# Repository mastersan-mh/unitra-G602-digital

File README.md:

I apologize to non-Russian-speaking users for the lack of information in English.

Данный проект был начат мной как попытка реанимировать старый электрофон Вега 119 с ЭПУ Unitra G602
(А ещё я люблю музыку и программирование).
Поскольку у оригинального устройства аналоговая плата управления пришла в полную негодность,
мной было принято решение о разработке цифрового управления.

В качестве платформы я выбрал Arduino Nano на микроконтроллере ATmega328p.
Это сильно упростило разработку платы и монтаж микросхем, особенно учитывая то, что это штучное устройство,
и весь монтаж я планировал провоизводить на макетную плату, используя только выводные компоненты.

Я процессе модернизации я старался как можно меньше модифицировать оригинальный компоненты,
однако, модификации подверглись:

1. Ведомый шкив. К нему снизу были приклеены 8 флажков.
Поскольку мне неизвестно передаточное число для шкива мотора и шкива диска,
я снимаю показания о скорости непосредственно со шкива диска.
Флажки изначально были подобраны такой высоты, чтобы шкив задевал ими за стол и не вращался.
Для того чтобы флажки стали нужной высоты, я покрыл наждачной бумагой стол ЭПУ, и несколько раз повернул шкив вокруг оси.
Как результат, флажки сточились до необходимой высоты.

2. В столе было прорезано одно отверстие, для того чтобы поместить туда оптический датчик для снятия показаний вращения диска,
и расширено одно из отверстий, чтобы в него вставить оптический датчик вращения двигателя.
Оригинальный датчик я не стал оставлять, поскольку его характеристики мне неизвестны,
а так же был сломан держатель лампы, которая освещала его.

3. Крепление двигателя было модифицировано, чтобы в него можно было вставить датчик вращения.

4. Оригиналная лампа стробоскопа была заменена на светодиод, который к тому же используется для индикации состояний.

5. Немного пришлось отрегулировать флажок автостопа, поскольку новый датчик немного не попал на то место, где находился старый датчик.

На самом деле, датчик вращения двигателя не нужен, я решил его установить в качестве эксперимена.

2019-09-29

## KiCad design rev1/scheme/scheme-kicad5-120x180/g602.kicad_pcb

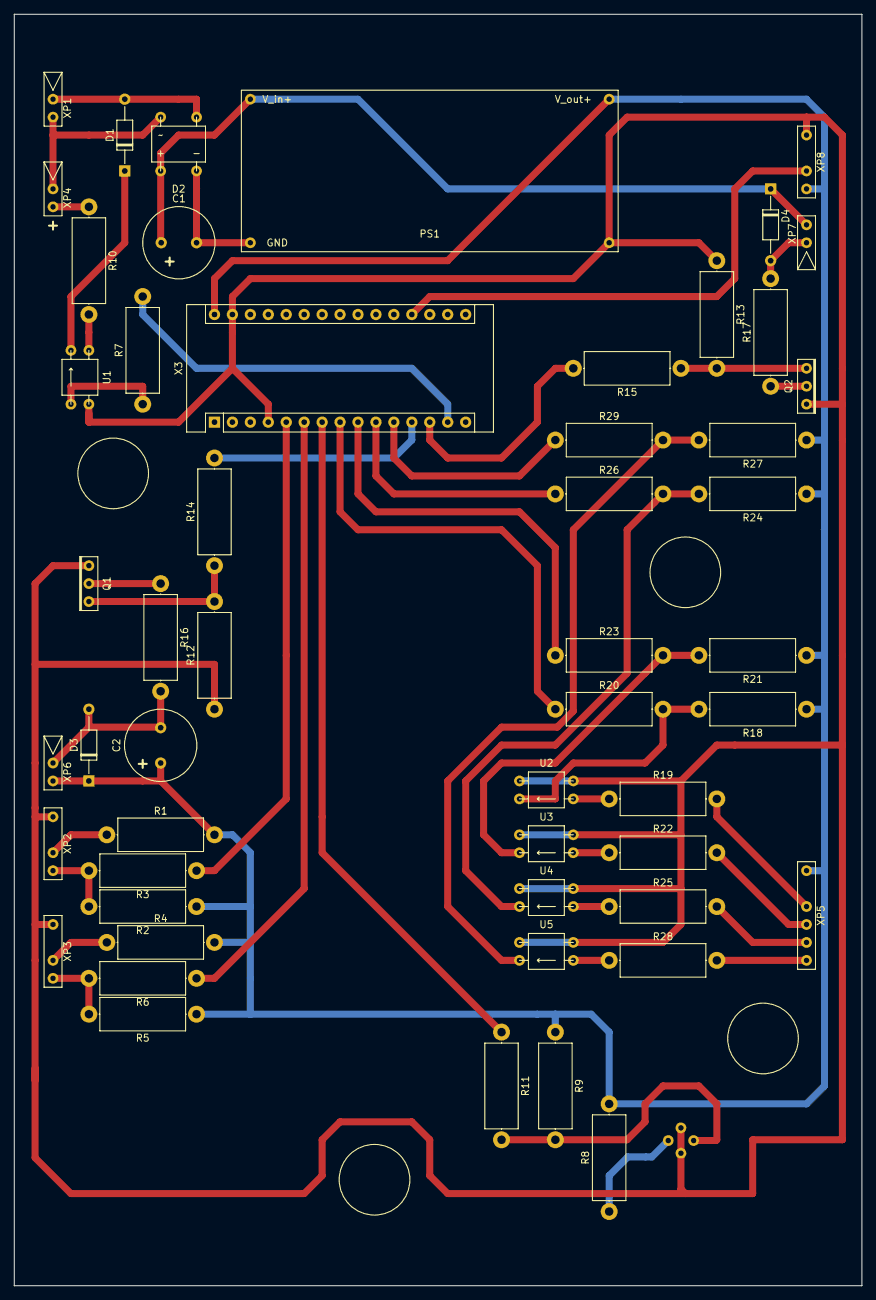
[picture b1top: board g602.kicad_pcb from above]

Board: 2 copper layers, 120.0 x 180.0 mm, 53 parts (1 on the bottom side), 45 nets.

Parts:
C1: 2500uF; C_Radial_D10.0mm_H12.5mm_P5.00mm
C2: 2200uF; C_Radial_D10.0mm_H12.5mm_P5.00mm
D1, D3, D4: D; D_DO-35_SOD27_P10.16mm_Horizontal
D2: DF01M
PS1: DC-DC; DC-DC-converter
Q1, Q2: IRL2203NPBF
R1, R4, R7, R8, R19, R22, R25, R28: 510; R_Axial_DIN0414_L11.9mm_D4.5mm_P15.24mm_Horizontal
R2, R5, R9, R18, R21, R24, R27: 10k; R_Axial_DIN0414_L11.9mm_D4.5mm_P15.24mm_Horizontal
R3, R6, R11, R20, R23, R26, R29: 1k; R_Axial_DIN0414_L11.9mm_D4.5mm_P15.24mm_Horizontal
R10: 2k; R_Axial_DIN0414_L11.9mm_D4.5mm_P15.24mm_Horizontal
R12, R13: 50k; R_Axial_DIN0414_L11.9mm_D4.5mm_P15.24mm_Horizontal
R14, R15: 10; R_Axial_DIN0414_L11.9mm_D4.5mm_P15.24mm_Horizontal
R16: 60; R_Axial_DIN0414_L11.9mm_D4.5mm_P15.24mm_Horizontal
R17: 200; R_Axial_DIN0414_L11.9mm_D4.5mm_P15.24mm_Horizontal
U1, U2, U3, U4, U5: PC817
X3: arduino-nano; Arduino_Nano
X4: TCST1103; TCST1103-veritcal
XP1: ~~ 50Hz, 17V; Connector_01x02
XP2: Feedback_drive; Connector_01x03
XP3: Feedback_table; Connector_01x03
XP4: Strobe; Connector_01x02
XP5: Buttons; Connector_01x05
XP6: Motor; Connector_01x02
XP7: Microlift; Connector_01x02
XP8: Manual_speed_adjust; Connector_01x03

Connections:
GNDREF: PS1.3, Q1.3, Q2.3, R12.1, R13.1, U1.2, U2.2, U2.3, U3.2, U3.3, U4.2, U4.3, U5.2, U5.3, X3.4, X3.29, X4.2, X4.4, XP2.1, XP3.1, XP8.1
unnamed: C1.1, D2.1, D4.1, PS1.1, XP7.2
unnamed: C1.2, D2.2, PS1.2
unnamed: C2.1, D3.1, PS1.4, R1.2, R2.1, R4.2, R5.1, R8.2, R9.1, R18.1, R21.1, R24.1, R27.1, X3.30, XP5.1, XP6.2, XP8.3
unnamed: C2.2, D3.2, R16.2, XP6.1
unnamed: D1.1, U1.4
unnamed: D1.2, D2.3, XP1.1
unnamed: D2.4, XP1.2, XP4.1
unnamed: D4.2, R17.2, XP7.1
unnamed: Q1.1, R12.2, R14.1
unnamed: Q1.2, R16.1
unnamed: Q2.1, R13.2, R15.1
unnamed: Q2.2, R17.1
unnamed: R1.1, XP2.2
unnamed: R2.2, R3.2, XP2.3
unnamed: R3.1, X3.5
unnamed: R4.1, XP3.2
unnamed: R5.2, R6.2, XP3.3
unnamed: R6.1, X3.6
unnamed: R7.1, U1.1
unnamed: R7.2, X3.14
unnamed: R8.1, X4.1
unnamed: R10.1, XP4.2
unnamed: R10.2, U1.3
unnamed: R11.1, X3.7
unnamed: R9.2, R11.2, X4.3
unnamed: R14.2, X3.12
unnamed: R15.2, X3.13
unnamed: R18.2, R20.2, U2.4
unnamed: R19.1, U2.1
unnamed: R19.2, XP5.2
unnamed: R20.1, X3.8
unnamed: R21.2, R23.2, U3.4
unnamed: R22.1, U3.1
unnamed: R22.2, XP5.3
unnamed: R23.1, X3.9
unnamed: R24.2, R26.2, U4.4
unnamed: R25.1, U4.1
unnamed: R25.2, XP5.4
unnamed: R26.1, X3.10
unnamed: R27.2, R29.2, U5.4
unnamed: R28.1, U5.1
unnamed: R28.2, XP5.5
unnamed: R29.1, X3.11
unnamed: X3.19, XP8.2

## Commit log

2019-09-27 (refs scheme) Scheme added.
2019-09-27 (refs scheme) Resisor updated.
2019-09-27 (refs src) sources draft added.
2019-09-28 (refs src) class renamed: G602 -> Ctrl
2019-09-28 (refs src) button fixed.
2019-09-28 (refs src) src: fixed speed measuring.
2019-09-29 (refs src) blinker added.
2019-09-29 (refs src) src: refactored, new blinks drafts added.
2019-09-29 (refs docs) documentation added.
2019-09-29 (refs src) blinker refactored.
2019-09-30 (refs src) refactored.
2019-10-01 (refs src) GBlinkerPetterned refactored, GBlinker added.
2019-10-01 (refs src) G602 refactored.
2019-10-01 (refs src) G602 incapsulation refactored.
2019-10-01 (refs docs) readme added.
2019-10-01 (refs src) service mode #1 added.
2019-10-01 (refs src) warnings fixed, blinks updated.
2019-10-02 (refs src) lib fixed.
2019-10-02 (refs src) tools draft added (PID).
2019-10-02 (refs src) tools: function analysis aded.
2019-10-02 (refs src) .gitignore added
2019-10-03 (refs src) serial port draft added.
2019-10-03 (refs src) trash removed.
2019-10-04 (refs src) update behaviour to make ability to add serial exchange.
2019-10-04 (refs src) communication calss draft added.
2019-10-07 (refs src) RPC added.
2019-10-08 (refs src) RPC client draft.
2019-10-09 (refs src) docs updated, src refactored.
2019-10-09 (refs src) Draft of Device class added.
2019-10-10 (refs src) Device class draft in progress.
2019-10-12 (refs src) fix firmware, fix tool.
2019-10-12 (refs src) pid koef fixed.
2019-10-12 (refs src) plots refactored.
2019-10-15 (refs src) tools refactored.
2019-10-15 (refs src) firmware and tool draft fix.
2019-10-15 (refs src) pid fixed.
2019-10-15 (refs src) increase the pulses per revolution on table.
2019-10-15 (refs src) potentiometer fixed.
2019-10-15 (refs src) moto state updating fixed.
2019-10-15 (refs src) debounce time changed.
2019-10-16 (refs lib) const reverse iterator added.
2019-10-16 (refs src) G602 methods visibility changed.
2019-10-16 (refs src) pulses count method changed.
2019-10-16 (refs src) regilator draft ready: ~90sec to enter to setpoint speed.
2019-10-16 (refs src) files structure changed.
2019-10-17 (refs src) event send on autostop fixed.
2019-10-17 (refs src) More incapsulation!
2019-10-17 (refs src) 1) decrease amount of schedulers to optimise memory usage; 2) remove unused objects.
2019-10-17 (refs docs) docs updated.
2019-10-17 (refs libs) isScheduled() method added.
2019-10-17 (refs src) double scheduling fixed.
2019-10-18 (refs #2) scheme: Back R16 to 10 Ohm to make regulation easy.
2019-10-18 (refs #2) tools: fix datatype conversion.
2019-10-19 (refs #2) firmware: set more effective PID coefficients.
2019-10-19 (refs #2) Added simple filter on speed warning.
2019-10-19 (refs #2) firmware: set more effective PID coefficients.
    * (refs #2) scheme: Back R16 to 10 Ohm to make regulation easy.
    * (refs #2) tools: fix datatype conversion.
    * (refs #2) firmware: set more effective PID coefficients.
    * (refs #2) Added simple filter on speed warning.
2019-10-19 (refs draft) tools: config store added.
2019-10-19 (refs draft) tools: Kswitch refactored.
2019-10-20 (refs draft) tools: more compact view.
2019-10-20 (refs draft) tools: remove no matter options from settings dialog.
2019-10-20 (refs draft) tools: Fix the console.
2019-10-20 (refs #4) Tools: Make more compact view (#5)
    * (refs #4) Tools: config store added.
    * (refs #4) Tools: Kswitch refactored.
    * (refs #4) Tools: more compact view.
    * (refs #4) Tools: remove no matter options from settings dialog.
    * (refs #4) Tools: Fix the console.
2019-10-20 (refs #) firmware: stop blinking on speed error while autosop.
2019-10-20 (refs #6) firmware: Stop blinking on speed error when autostop triggered.
2019-11-11 (refs #8) firmware: time window changed to make time is integer.
2019-11-11 (refs #8) More effective coefficients (about 7 seconds to pv=sp)
2019-11-11 (refs #8) Make more effective coefficients and faster reaching the setpoint speed. (#9)
    * (refs #8) firmware: time window changed to make time is integer.
    * (refs #8) More effective coefficients (about 7 seconds to pv=sp)
2019-11-14 (refs #) tools: added some good buttons.
2019-11-23 (refs #) tools: refactored.
2019-11-23 (refs #) firmware: namespace changed.
2019-12-12 (refs #none) refactored (#10)
    * (refs #) tools: added some good buttons.
    * (refs #) tools: refactored.
    * (refs #) firmware: namespace changed.
2019-12-12 (refs #none) Pictures added.
2023-01-15 tool fix
2023-01-17 Eff C++
2023-01-21 Eff C++ 2
2023-01-21 Increased amount of impulses per revolution
2023-01-21 Update FixedPointer
2023-01-21 Eff C++ 3
2023-01-23 refactored
